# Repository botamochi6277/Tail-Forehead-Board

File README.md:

# Tail Forehead Board

Eagle PCB Design of a forehead board of [Hacka-Tail](https://botalab.tech/hacka-tail/) Whale

The board has connectors for M5Atom and Tail-Disk board, respectively.

## LICENCE

Open Source Hardware

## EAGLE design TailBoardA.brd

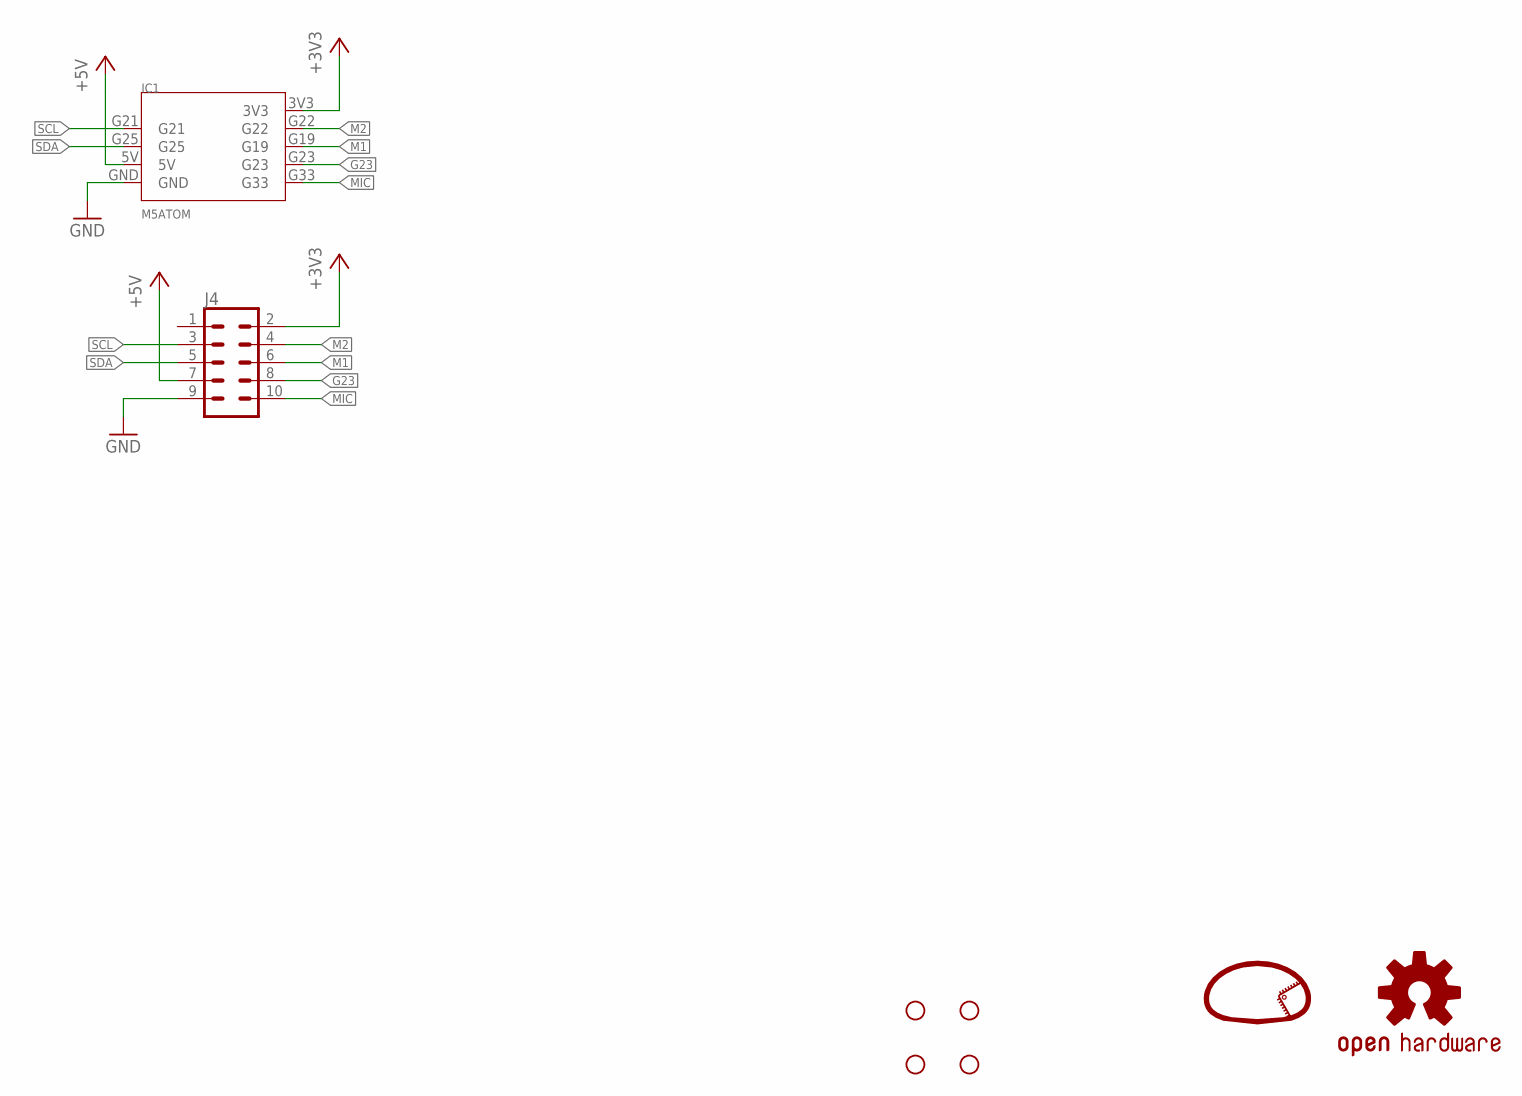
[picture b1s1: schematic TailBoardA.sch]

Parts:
H1, H2, H3, H4: STAND-OFF2.1; STAND-OFF-2.1
IC1: M5ATOM
J4: CONN_05X2SHD; 2X5-SHROUDED
LOGO1: LOGO
LOGO2: OSHW-LOGOS; OSHW-LOGO-S

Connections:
+3V3: IC1.3V3, J4.2
+5V: IC1.5V, J4.7
G23: IC1.G23, J4.8
GND: IC1.GND, J4.9
M1: IC1.G19, J4.6
M2: IC1.G22, J4.4
MIC: IC1.G33, J4.10
SCL: IC1.G21, J4.3
SDA: IC1.G25, J4.5

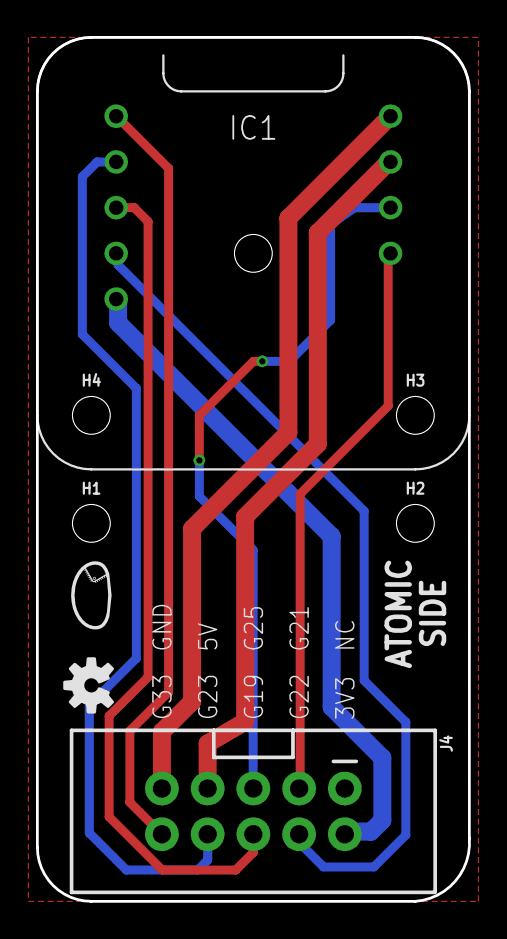
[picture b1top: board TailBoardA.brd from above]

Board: 2 copper layers, 24.0 x 48.0 mm, 8 parts (0 on the bottom side), 9 nets.

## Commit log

2021-08-28 add design

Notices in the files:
parts and their libraries:
SparkFun-Aesthetics: Licensing: Creative Commons ShareAlike 4.0 International - https://creativecommons.org/licenses/by-sa/4.0
